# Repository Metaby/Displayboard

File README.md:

# Displayboard
This is the repository for my free time project. I developed the circuits to drive an DOGXL display with touchpanel from Electronic Assembly. It is driven by two Atmel microcontrollers. One ATtiny for the Touchpanel multiplexing and reading and one ATmega for driving the display itself (simple operating system, graphics driver).
The project is split into three parts
- Circuits, EAGLE files for the circuit board
- TPU, The touchpanel driver/firmware for the ATtiny
- GPU, The display driver/firmware (including a simple operating system) for the ATmega

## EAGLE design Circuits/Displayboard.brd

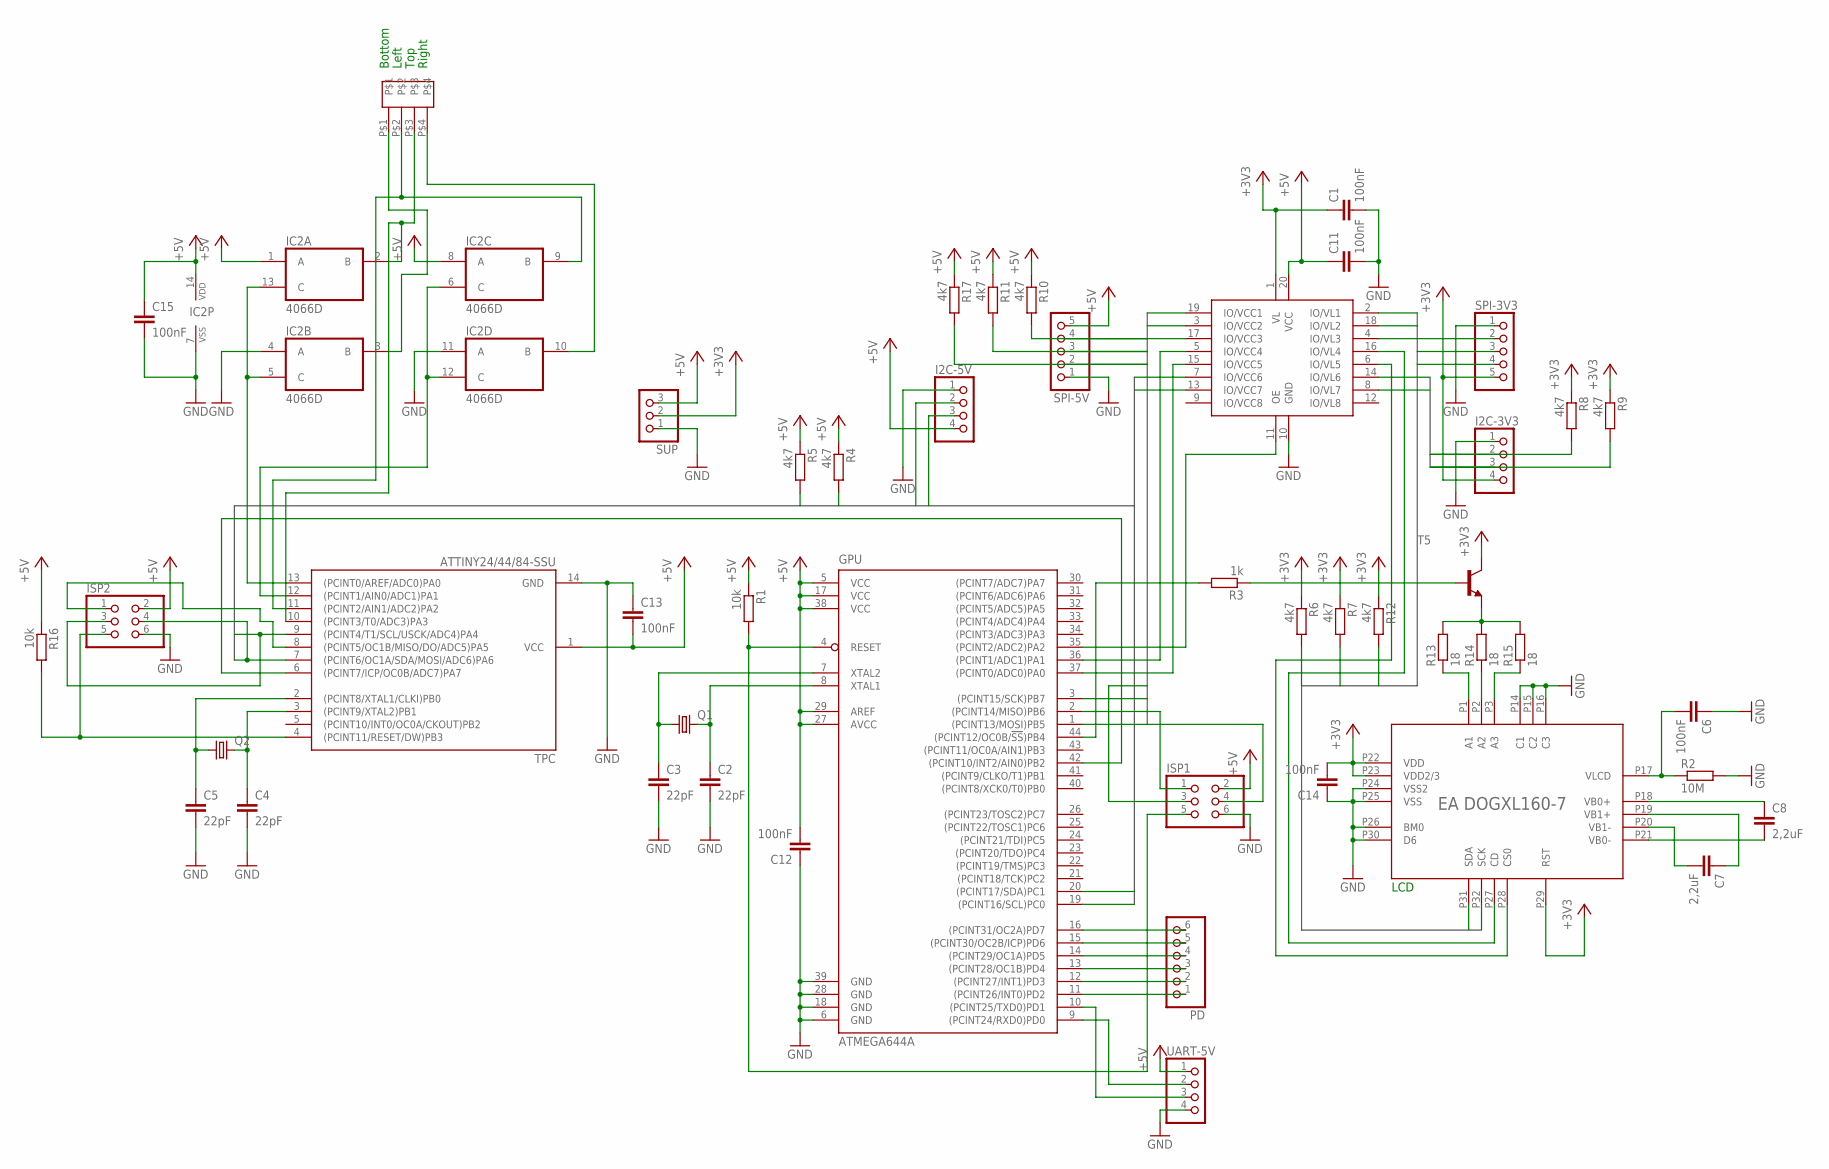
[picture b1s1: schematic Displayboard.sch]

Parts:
C1, C6, C11, C12, C13, C14, C15: 100nF; C1206
C2, C3, C4, C5: 22pF; C1206
C7, C8: 2,2uF; C1206
EADOGXL160-7: DOGXL
GPU: ATMEGA644A; TQFP44
I2C-3V3, I2C-5V: PINHD-1X4/90; 1X04/90
IC1: ST2378; TSSOP-20
IC2: 4066D; SO14
ISP1, ISP2: PINHD-2X3/90; 2X03/90
PD: PINHD-1X6/90; 1X06/90
Q1, Q2: CRYSTALHC49UP; HC49UP
R1, R16: 10k; R1206
R2: 10M; R1206
R3: 1k; R1206
R4, R5, R6, R7, R8, R9, R10, R11, R12, R17: 4k7; R1206
R13, R14, R15: 18; R1206
SPI-3V3, SPI-5V: PINHD-1X5/90; 1X05/90
SUP: PINHD-1X3/90; 1X03/90
T5: BCX19-NPN-SOT23-BEC; SOT23-BEC
TPC: ATTINY24/44/84-SSU; SOIC14
U$1: ZIF-4-1
UART-5V: PINHD-1X4/90; 1X04/90

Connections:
+3V3: C1.1, C14.2, EADOGXL160-7.P22 (VDD), EADOGXL160-7.P23 (VDD2/3), EADOGXL160-7.P29 (RST), I2C-3V3.4, IC1.1 (VL), R6.1, R7.1, R8.1, R9.1, R12.1, SPI-3V3.5, SUP.2, T5.C
+5V: C11.1, C12.2, C13.2, C15.1, GPU.5 (VCC), GPU.17 (VCC), GPU.27 (AVCC), GPU.29 (AREF), GPU.38 (VCC), I2C-5V.4, IC1.20 (VCC), IC2.1 (A), IC2.8 (A), IC2.14 (VDD), ISP1.2, ISP2.2, R1.1, R4.1, R5.1, R10.1, R11.1, R16.1, R17.1, SPI-5V.5, SUP.3, TPC.1 (VCC), UART-5V.1
GND: C1.2, C2.2, C3.2, C4.2, C5.2, C6.1, C11.2, C12.1, C13.1, C14.1, C15.2, EADOGXL160-7.P14 (C1), EADOGXL160-7.P15 (C2), EADOGXL160-7.P16 (C3), EADOGXL160-7.P24 (VSS2), EADOGXL160-7.P25 (VSS), EADOGXL160-7.P26 (BM0), EADOGXL160-7.P30 (D6), GPU.6 (GND), GPU.18 (GND), GPU.28 (GND), GPU.39 (GND), I2C-3V3.1, I2C-5V.1, IC1.10 (GND), IC2.4 (A), IC2.7 (VSS), IC2.11 (A), ISP1.6, ISP2.6, R2.2, SPI-3V3.1, SPI-5V.1, SUP.1, TPC.14 (GND), UART-5V.4
MISO: GPU.2 ((PCINT14/MISO)PB6), IC1.3 (IO/VCC2), ISP1.1, R10.2, SPI-5V.4
MISO3: IC1.18 (IO/VL2), R6.2, SPI-3V3.4
MOSI: GPU.1 ((PCINT13/MOSI)PB5), IC1.17 (IO/VCC3), ISP1.4, R11.2, SPI-5V.3
MOSI3: EADOGXL160-7.P31 (SDA), IC1.4 (IO/VL3), R7.2, SPI-3V3.3
unnamed: C3.1, GPU.7 (XTAL2), Q1.1
unnamed: C2.1, GPU.8 (XTAL1), Q1.2
unnamed: GPU.4 (RESET), ISP1.5, R1.2
unnamed: C5.1, Q2.1, TPC.2 ((PCINT8/XTAL1/CLKI)PB0)
unnamed: C4.1, Q2.2, TPC.3 ((PCINT9/XTAL2)PB1)
unnamed: C6.2, EADOGXL160-7.P17 (VLCD), R2.1
unnamed: IC2.2 (B), TPC.10 ((PCINT3/T0/ADC3)PA3), U$1.P$3
unnamed: C8.1, EADOGXL160-7.P18 (VB0+)
unnamed: C7.1, EADOGXL160-7.P19 (VB1+)
unnamed: C7.2, EADOGXL160-7.P20 (VB1-)
unnamed: C8.2, EADOGXL160-7.P21 (VB0-)
unnamed: GPU.36 ((PCINT1/ADC1)PA1), IC1.5 (IO/VCC4)
unnamed: IC2.9 (B), TPC.11 ((PCINT2/AIN1/ADC2)PA2), U$1.P$2
unnamed: IC2.3 (B), U$1.P$1
unnamed: GPU.16 ((PCINT31/OC2A)PD7), PD.6
unnamed: IC2.5 (C), IC2.13 (C), TPC.13 ((PCINT0/AREF/ADC0)PA0)
unnamed: IC2.6 (C), IC2.12 (C), TPC.12 ((PCINT1/AIN0/ADC1)PA1)
unnamed: IC2.10 (B), U$1.P$4
unnamed: GPU.42 ((PCINT10/INT2/AIN0)PB2), TPC.6 ((PCINT7/ICP/OC0B/ADC7)PA7)
unnamed: GPU.15 ((PCINT30/OC2B/ICP)PD6), PD.5
unnamed: GPU.14 ((PCINT29/OC1A)PD5), PD.4
unnamed: EADOGXL160-7.P27 (CD), IC1.16 (IO/VL4)
unnamed: GPU.13 ((PCINT28/OC1B)PD4), PD.3
unnamed: EADOGXL160-7.P28 (CS0), IC1.6 (IO/VL5)
unnamed: GPU.37 ((PCINT0/ADC0)PA0), IC1.15 (IO/VCC5)
unnamed: GPU.12 ((PCINT27/INT1)PD3), PD.2
unnamed: GPU.35 ((PCINT2/ADC2)PA2), IC1.11 (OE)
unnamed: GPU.11 ((PCINT26/INT0)PD2), PD.1
unnamed: GPU.10 ((PCINT25/TXD0)PD1), UART-5V.3
unnamed: GPU.9 ((PCINT24/RXD0)PD0), UART-5V.2
unnamed: R3.1, T5.B
unnamed: EADOGXL160-7.P3 (A3), R15.1
unnamed: EADOGXL160-7.P2 (A2), R14.1
unnamed: EADOGXL160-7.P1 (A1), R13.1
unnamed: R13.2, R14.2, R15.2, T5.E
unnamed: ISP2.5, R16.2, TPC.4 ((PCINT11/RESET/DW)PB3)
unnamed: GPU.44 ((PCINT12/OC0B/!SS!)PB4), R3.2
unnamed: ISP2.1, TPC.8 ((PCINT5/OC1B/MISO/DO/ADC5)PA5)
SCK: GPU.3 ((PCINT15/SCK)PB7), IC1.19 (IO/VCC1), ISP1.3, R17.2, SPI-5V.2
SCK3: EADOGXL160-7.P32 (SCK), IC1.2 (IO/VL1), R12.2, SPI-3V3.2
SCL: GPU.19 ((PCINT16/SCL)PC0), I2C-5V.2, IC1.7 (IO/VCC6), ISP2.3, R5.2, TPC.9 ((PCINT4/T1/SCL/USCK/ADC4)PA4)
SCL3: I2C-3V3.2, IC1.14 (IO/VL6), R8.2
SDA: GPU.20 ((PCINT17/SDA)PC1), I2C-5V.3, IC1.13 (IO/VCC7), ISP2.4, R4.2, TPC.7 ((PCINT6/OC1A/SDA/MOSI/ADC6)PA6)
SDA3: I2C-3V3.3, IC1.8 (IO/VL7), R9.2

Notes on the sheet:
LCD
Bottom
Left
Top
Right

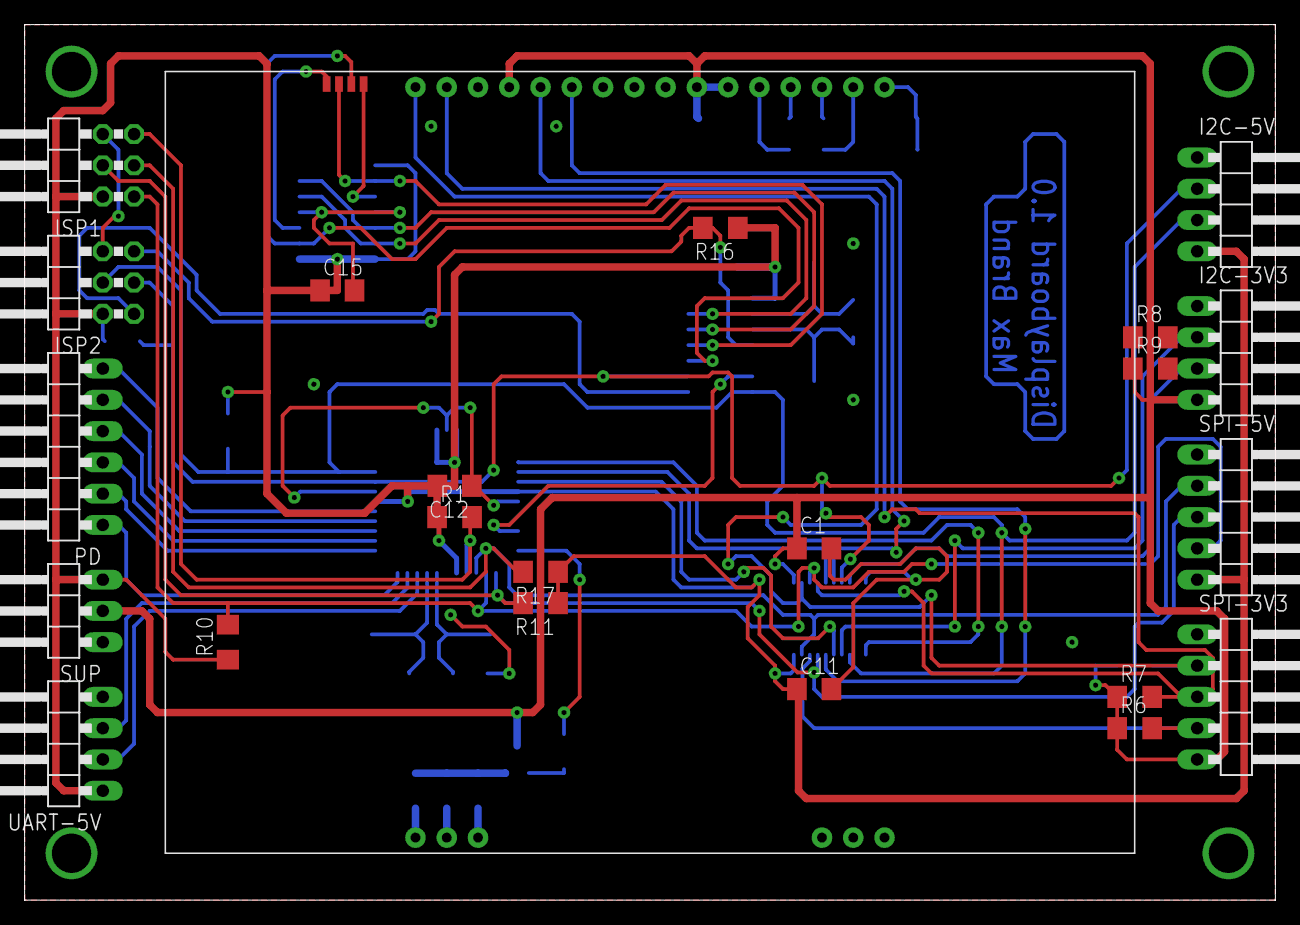
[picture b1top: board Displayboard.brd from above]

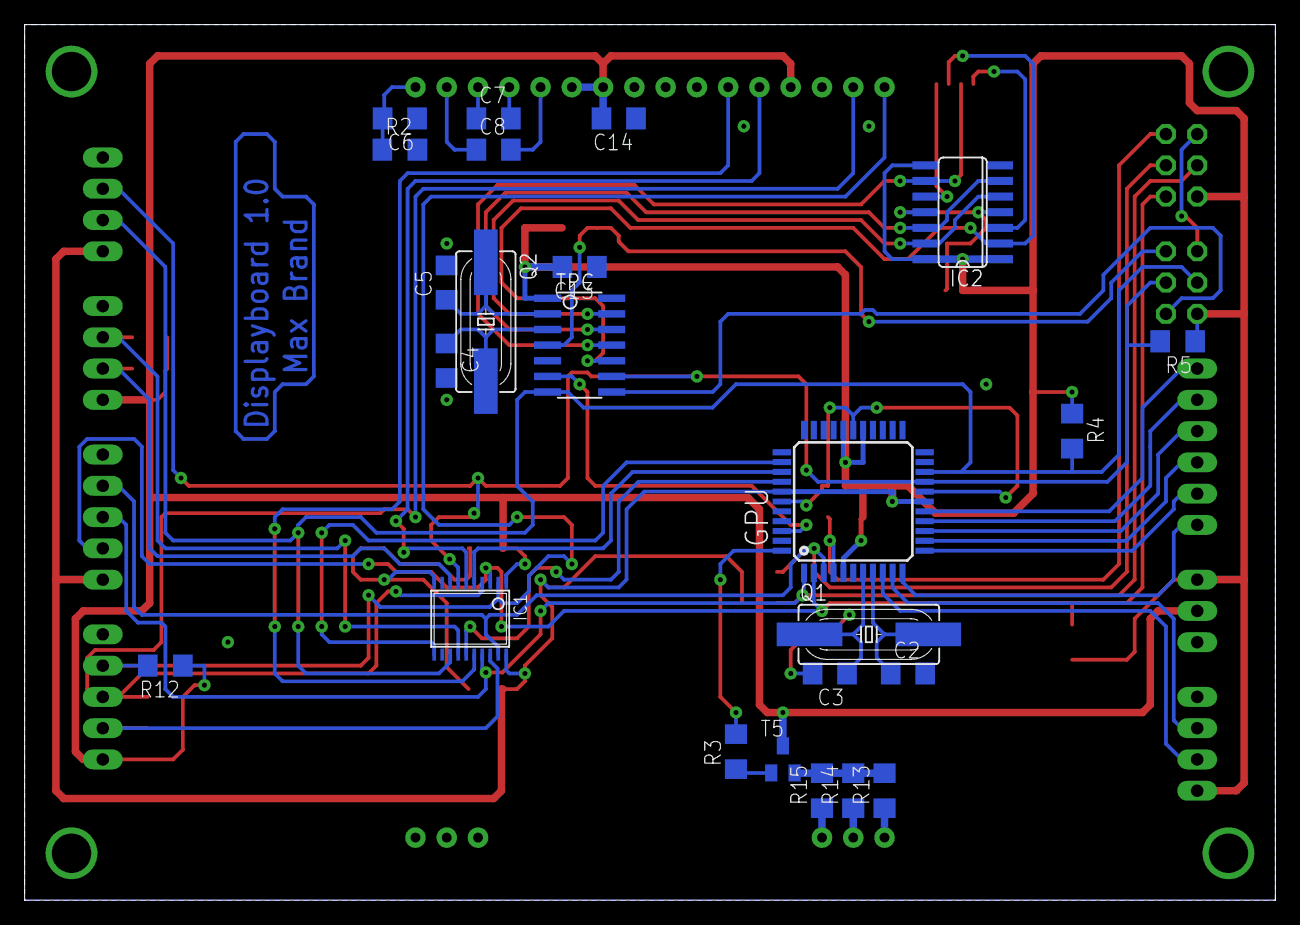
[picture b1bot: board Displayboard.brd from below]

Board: 2 copper layers, 101.6 x 71.1 mm, 48 parts (24 on the bottom side), 51 nets.

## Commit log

2017-02-07 Init
    Initial commit of existing project.
2017-04-09 Fixed bugs and improved the kernel
    + Print numbers bug fixed
    + listening on rs232 port is now a kernel program
    + created operating_system program, not finished
2017-04-09 Improvements and bug fixes on operating system and kernel
    + Added touch_function for programs
    // Interrupt problem on dev board, need to fix this first
2017-08-30 Started to develop the robot remote control program
    -> created basic construct of robot_control
2017-09-03 Bugfixes, Font improvment
    + Fixed some bugs that broke the touch function.
    + Removed the operating system function and improved the kernel. The kernel now runs the operating system directly.
    + Remade the font for better readability.
